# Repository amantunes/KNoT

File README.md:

# KNoT High Precision IoT Sensor Node

This sensor node was developed as a master's thesis project, with the objective of achieving high precision measurements of several sensors of any type, including those which can present some challenges such as water conductivity or pH sensors.

In order to achieve this a Cypress PSoC 5LP Microcontroller was used due to its 20-bit internal ADC, alongside an optional Analog Devices AD5941 High Precision, Impedance & Electrochemical Front End.

Wired communications are handled by various protocols, such as I2C, SPI and UART, while wireless communications are handled by a u-blox SARA N2 NB-IoT module.

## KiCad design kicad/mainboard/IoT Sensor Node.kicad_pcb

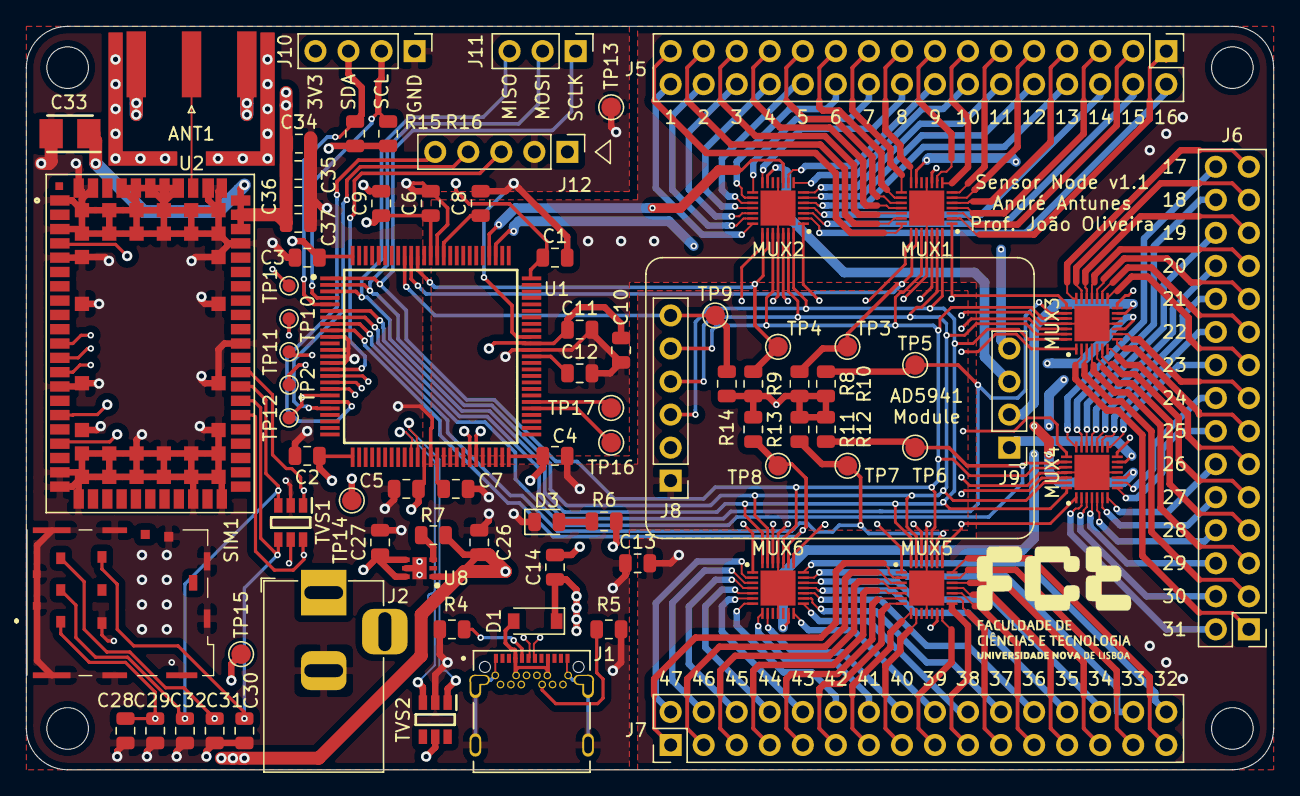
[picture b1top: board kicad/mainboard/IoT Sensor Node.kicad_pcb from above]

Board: 4 copper layers, 95.9 x 57.2 mm, 81 parts (0 on the bottom side), 147 nets.

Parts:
ANT1: Conn_Coaxial; SMA_Amphenol_132289_EdgeMount
C1, C2, C3, C4, C5, C6, C11, C28, C34: 0.1uF; C_0805_2012Metric
C7, C8, C9, C10, C12, C13, C14: 1uF; C_0805_2012Metric
C26, C27: 4.7uF; C_0805_2012Metric
C29, C30, C31, C32: 33pF; C_0805_2012Metric
C33: 100uF; CAPPM3528X210N
C35: 10nF; C_0805_2012Metric
C36: 68pF; C_0805_2012Metric
C37: 15pF; C_0805_2012Metric
D1: PMEG2010ER; D_SOD-123
D3: LED; LED_0805_2012Metric
J1: UJ31-CH-31N-SMT-TR; CUI_UJ31-CH-3-SMT-TR
J2: Jack-DC; BarrelJack_Horizontal
J5, J7: Conn_02x16_Odd_Even; PinHeader_2x16_P2.54mm_Vertical
J6: Conn_02x15_Odd_Even; PinHeader_2x15_P2.54mm_Vertical
J8: Conn_01x06; PinHeader_1x06_P2.54mm_Vertical
J9, J10: Conn_01x04; PinHeader_1x04_P2.54mm_Vertical
J11: Conn_01x03; PinHeader_1x03_P2.54mm_Vertical
J12: Conn_01x05; PinHeader_1x05_P2.54mm_Vertical
MUX1, MUX2, MUX3, MUX4, MUX5, MUX6: MAX14661ETI+; QFN40P400X400X80-29N
R4, R5: 5.1KR; R_0805_2012Metric
R6: 1KR; R_0805_2012Metric
R7, R8, R9, R10, R11, R12, R13, R14, R15, R16: 10KR; R_0805_2012Metric
SIM1: SF72S006VBAR2500
TP1, TP2, TP10, TP11, TP12: TestPoint; TestPoint_Pad_D1.0mm
TP3, TP4, TP5, TP6, TP7, TP8, TP9, TP13, TP14, TP15, TP16, TP17: TestPoint; TestPoint_Pad_D1.5mm
TVS1, TVS2: CM1293A-04SO; SOP95P275X110-6N
U1: CY8C5888AXI-LP096; QFP50P1600X1600X145-100N
U2: SARA-N210
U8: LP5912-3.3DRVR; SON65P200X200X80-7N

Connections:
3.3V: C3.1, C26.1, C33.1, C34.1, C35.1, C36.1, C37.1, J8.2, J10.4, MUX1.1, MUX1.22, MUX1.26, MUX2.1, MUX2.22, MUX2.26, MUX3.1, MUX3.22, MUX3.26, MUX4.1, MUX4.22, MUX4.26, MUX5.1, MUX5.22, MUX5.26, MUX6.1, MUX6.22, MUX6.26, R6.2, R7.2, R8.2, R9.2, R10.2, R11.2, R12.2, R13.2, R14.2, R15.2, R16.2, TP15.1, U1.100, U2.51, U2.52, U2.53, U8.1
AD5941_CS: J8.6, R14.1, TP9.1, U1.92
I2C_3V3_SCL: J10.2, R16.1, U1.4
I2C_3V3_SDA: J10.3, R15.1, U1.5
MUX1_1: J5.1, MUX1.2
MUX1_2: J5.3, MUX1.3
MUX1_3: J5.5, MUX1.4
MUX1_4: J5.7, MUX1.5
MUX1_5: J5.9, MUX1.6
MUX1_6: J5.11, MUX1.7
MUX1_7: J5.13, MUX1.8
MUX1_8: J5.15, MUX1.9
MUX1_9: J5.31, MUX1.21
MUX1_10: J5.29, MUX1.20
MUX1_11: J5.27, MUX1.19
MUX1_12: J5.25, MUX1.18
MUX1_13: J5.23, MUX1.17
MUX1_14: J5.21, MUX1.16
MUX1_15: J5.19, MUX1.15
MUX1_16: J5.17, MUX1.14
MUX1_A: MUX1.10, U1.78
MUX1_B: J9.4, MUX1.13
MUX1_CS: MUX1.23, R8.1, TP3.1, U1.91
MUX2_1: J5.2, MUX2.2
MUX2_2: J5.4, MUX2.3
MUX2_3: J5.6, MUX2.4
MUX2_4: J5.8, MUX2.5
MUX2_5: J5.10, MUX2.6
MUX2_6: J5.12, MUX2.7
MUX2_7: J5.14, MUX2.8
MUX2_8: J5.16, MUX2.9
MUX2_9: J5.32, MUX2.21
MUX2_10: J5.30, MUX2.20
MUX2_11: J5.28, MUX2.19
MUX2_12: J5.26, MUX2.18
MUX2_13: J5.24, MUX2.17
MUX2_14: J5.22, MUX2.16
MUX2_15: J5.20, MUX2.15
MUX2_16: J5.18, MUX2.14
MUX2_A: MUX2.10, U1.79
MUX2_B: J9.3, MUX2.13
MUX2_CS: MUX2.23, R9.1, TP4.1, U1.90
MUX3_1: J6.1, MUX3.2
MUX3_2: J6.3, MUX3.3
MUX3_3: J6.5, MUX3.4
MUX3_4: J6.7, MUX3.5
MUX3_5: J6.9, MUX3.6
MUX3_6: J6.11, MUX3.7
MUX3_7: J6.13, MUX3.8
MUX3_8: J6.15, MUX3.9
MUX3_9: J6.29, MUX3.21
MUX3_10: J6.27, MUX3.20
MUX3_11: J6.25, MUX3.19
MUX3_12: J6.23, MUX3.18
MUX3_13: J6.21, MUX3.17
MUX3_14: J6.19, MUX3.16
MUX3_15: J6.17, MUX3.15
MUX3_A: MUX3.10, U1.44
MUX3_B: J9.2, MUX3.13
MUX3_CS: MUX3.23, R10.1, TP5.1, U1.6
MUX4_1: J6.2, MUX4.2
MUX4_2: J6.4, MUX4.3
MUX4_3: J6.6, MUX4.4
MUX4_4: J6.8, MUX4.5
MUX4_5: J6.10, MUX4.6
MUX4_6: J6.12, MUX4.7
MUX4_7: J6.14, MUX4.8
MUX4_8: J6.16, MUX4.9
MUX4_9: J6.30, MUX4.21
MUX4_10: J6.28, MUX4.20
MUX4_11: J6.26, MUX4.19
MUX4_12: J6.24, MUX4.18
MUX4_13: J6.22, MUX4.17
MUX4_14: J6.20, MUX4.16
MUX4_15: J6.18, MUX4.15
MUX4_A: MUX4.10, U1.45
MUX4_B: J9.1, MUX4.13
MUX4_CS: MUX4.23, R11.1, TP6.1, U1.7
MUX5_1: J7.1, MUX5.2
MUX5_2: J7.3, MUX5.3
MUX5_3: J7.5, MUX5.4
MUX5_4: J7.7, MUX5.5
MUX5_5: J7.9, MUX5.6
MUX5_6: J7.11, MUX5.7
MUX5_7: J7.13, MUX5.8
MUX5_8: J7.15, MUX5.9
MUX5_9: J7.31, MUX5.21
MUX5_10: J7.29, MUX5.20
MUX5_11: J7.27, MUX5.19
MUX5_12: J7.25, MUX5.18
MUX5_13: J7.23, MUX5.17
MUX5_14: J7.21, MUX5.16
MUX5_15: J7.19, MUX5.15
MUX5_16: J7.17, MUX5.14
MUX5_B: MUX4.14, MUX5.13
MUX5_CS: MUX5.23, R12.1, TP7.1, U1.8
MUX6_1: J7.2, MUX6.2
MUX6_2: J7.4, MUX6.3
MUX6_3: J7.6, MUX6.4
MUX6_4: J7.8, MUX6.5
MUX6_5: J7.10, MUX6.6
MUX6_6: J7.12, MUX6.7
MUX6_7: J7.14, MUX6.8
MUX6_8: J7.16, MUX6.9
MUX6_9: J7.32, MUX6.21
MUX6_10: J7.30, MUX6.20
MUX6_11: J7.28, MUX6.19
MUX6_12: J7.26, MUX6.18
MUX6_13: J7.24, MUX6.17
MUX6_14: J7.22, MUX6.16
MUX6_15: J7.20, MUX6.15
MUX6_16: J7.18, MUX6.14
MUX6_B: MUX3.14, MUX6.13
MUX6_CS: MUX6.23, R13.1, TP8.1, U1.9
unnamed: D1.2, J1.A4, J1.A9, J1.B4, J1.B9
unnamed: D3.2, R6.1
unnamed: J1.A5, R4.1
unnamed: J1.B5, R5.1
unnamed: R7.1, U8.3
unnamed: TP1.1, U2.4
unnamed: TP2.1, U2.16
unnamed: TP16.1, U1.55
unnamed: TP17.1, U1.56
RST: J12.3, U1.15
SARA_ANT: ANT1.1, U2.56
SARA_CTS: U1.16, U2.11
SARA_RESET: TP12.1, U1.19, U2.18
SARA_RXD: TP11.1, U1.18, U2.13
SARA_SIM_CLK: C31.1, SIM1.C3, TVS1.6, U2.38
SARA_SIM_IO: C30.1, SIM1.C7, TVS1.4, U2.39
SARA_SIM_RST: C32.1, SIM1.C2, TVS1.3, U2.40
SARA_TXD: TP10.1, U1.17, U2.12
SARA_VSIM: C28.1, C29.1, SIM1.C1, TVS1.1, U2.41
SPI_MISO: J8.3, J11.3, MUX1.28, MUX2.28, MUX3.28, MUX4.28, MUX5.28, MUX6.28, U1.3
SPI_MOSI: J8.4, J11.2, MUX1.27, MUX2.27, MUX3.27, MUX4.27, MUX5.27, MUX6.27, U1.2
SPI_SCLK: J8.5, J11.1, MUX1.24, MUX2.24, MUX3.24, MUX4.24, MUX5.24, MUX6.24, U1.1
SWDCLK: J12.4, U1.21
SWDIO: J12.5, U1.20
USB+: J1.A6, J1.B6, TVS2.3, U1.35
USB-: J1.A7, J1.B7, TVS2.1, U1.36
VBAT: ANT1.2, C1.2, C2.2, C3.2, C4.2, C5.2, C6.2, C7.2, C8.2, C9.2, C13.1, C26.2, C27.2, C28.2, C29.2, C30.2, C31.2, C32.2, C33.2, C34.2, C35.2, C36.2, C37.2, D3.1, J1.A1, J1.A12, J1.B1, J1.B12, J1.SH1, J1.SH2, J1.SH3, J1.SH4, J1.SH5, J1.SH6, J2.2, J8.1, J10.1, J12.2, MUX1.11, MUX1.25, MUX1.29, MUX2.11, MUX2.25, MUX2.29, MUX3.11, MUX3.25, MUX3.29, MUX4.11, MUX4.25, MUX4.29, MUX5.11, MUX5.25, MUX5.29, MUX6.11, MUX6.25, MUX6.29, R4.2, R5.2, SIM1.C5, SIM1.GND1, SIM1.GND2, SIM1.GND3, SIM1.GND4, SIM1.GND5, SIM1.GND6, SIM1.GND7, SIM1.GND8, SIM1.GND9, SIM1.GND10, TP13.1, TVS1.2, TVS2.2, U1.10, U1.12, U1.13, U1.14, U1.38, U1.66, U1.87, U2.1, U2.3, U2.5, U2.14, U2.20, U2.21, U2.22, U2.30, U2.32, U2.43, U2.50, U2.54, U2.55, U2.57, U2.58, U2.59, U2.60, U2.61, U2.63, U2.64, U2.65, U2.66, U2.67, U2.68, U2.69, U2.70, U2.71, U2.72, U2.73, U2.74, U2.75, U2.76, U2.77, U2.78, U2.79, U2.80, U2.81, U2.82, U2.83, U2.84, U2.85, U2.86, U2.87, U2.88, U2.89, U2.90, U2.91, U2.92, U2.93, U2.94, U2.95, U2.96, U8.5, U8.7
VCC1: C7.1, U1.39
VCC2: C8.1, U1.86
VCCA: C12.1, U1.63
VDD1: C1.1, C2.1, C4.1, C5.1, C6.1, C9.1, C14.1, C27.1, D1.1, J2.1, J12.1, TP14.1, TVS1.5, TVS2.5, U1.26, U1.37, U1.50, U1.75, U1.88, U8.4, U8.6
VDDA: C10.1, C11.1, C14.2, U1.65
VSSA: C10.2, C11.2, C12.2, C13.2, U1.64

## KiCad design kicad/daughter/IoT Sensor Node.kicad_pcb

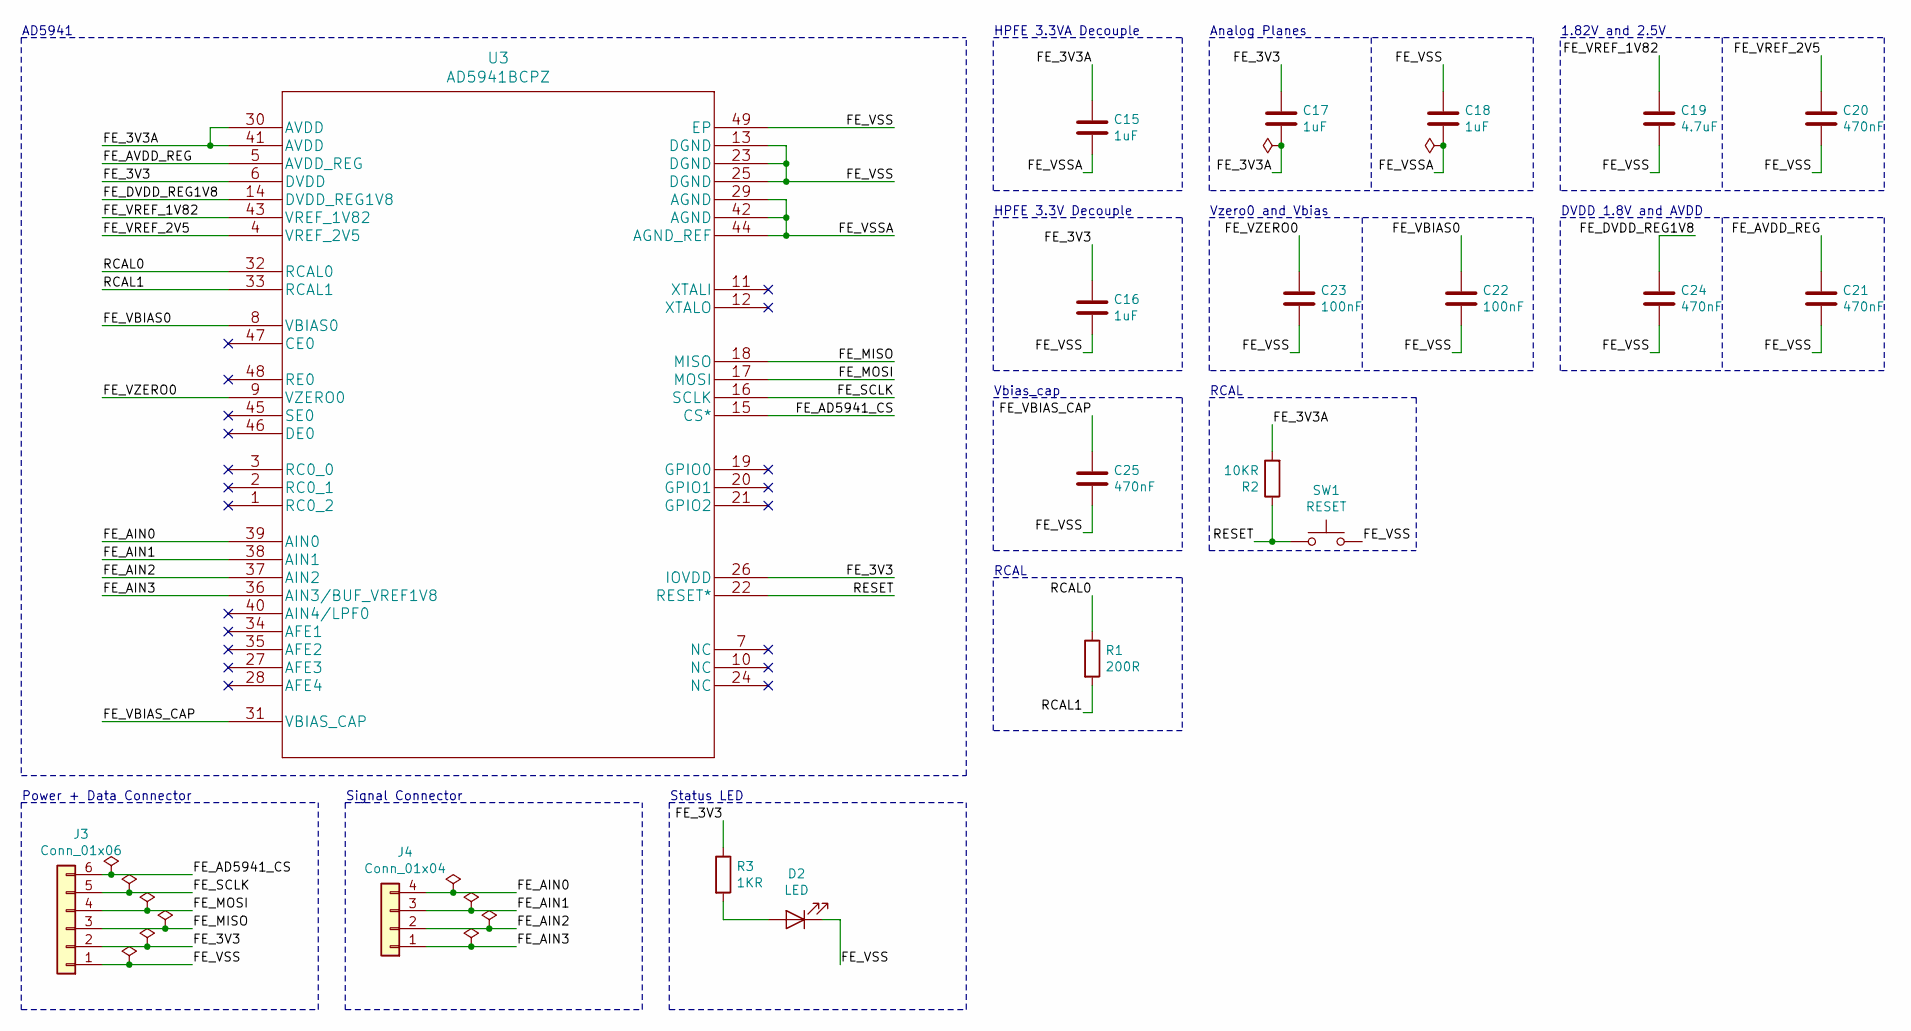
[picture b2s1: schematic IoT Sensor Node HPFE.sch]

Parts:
C15, C16, C17, C18: 1uF; C_0805_2012Metric
C19: 4.7uF; C_0805_2012Metric
C20, C21, C24, C25: 470nF; C_0805_2012Metric
C22, C23: 100nF; C_0805_2012Metric
D2: LED; LED_0805_2012Metric
J3: Conn_01x06; PinSocket_1x06_P2.54mm_Vertical
J4: Conn_01x04; PinSocket_1x04_P2.54mm_Vertical
R1: 200R; R_0805_2012Metric
R2: 10KR; R_0805_2012Metric
R3: 1KR; R_0805_2012Metric
SW1: RESET; PTS815SJM250SMTR
U3: AD5941BCPZ; QFN50P700X700X80-49N-D

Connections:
/IoT Sensor Node HPFE/FE_3V3: C16.1, C17.1, J3.2, R3.1, U3.6 (DVDD), U3.26 (IOVDD)
/IoT Sensor Node HPFE/FE_3V3A: C15.1, C17.2, R2.2, U3.30 (AVDD), U3.41 (AVDD)
/IoT Sensor Node HPFE/FE_AD5941_CS: J3.6, U3.15 (CS*)
/IoT Sensor Node HPFE/FE_AIN0: J4.4, U3.39 (AIN0)
/IoT Sensor Node HPFE/FE_AIN1: J4.3, U3.38 (AIN1)
/IoT Sensor Node HPFE/FE_AIN2: J4.2, U3.37 (AIN2)
/IoT Sensor Node HPFE/FE_AIN3: J4.1, U3.36 (AIN3/BUF_VREF1V8)
/IoT Sensor Node HPFE/FE_AVDD_REG: C21.1, U3.5 (AVDD_REG)
/IoT Sensor Node HPFE/FE_DVDD_REG1V8: C24.1, U3.14 (DVDD_REG1V8)
/IoT Sensor Node HPFE/FE_MISO: J3.3, U3.18 (MISO)
/IoT Sensor Node HPFE/FE_MOSI: J3.4, U3.17 (MOSI)
/IoT Sensor Node HPFE/FE_SCLK: J3.5, U3.16 (SCLK)
/IoT Sensor Node HPFE/FE_VBIAS0: C22.1, U3.8 (VBIAS0)
/IoT Sensor Node HPFE/FE_VBIAS_CAP: C25.1, U3.31 (VBIAS_CAP)
/IoT Sensor Node HPFE/FE_VREF_1V82: C19.1, U3.43 (VREF_1V82)
/IoT Sensor Node HPFE/FE_VREF_2V5: C20.1, U3.4 (VREF_2V5)
/IoT Sensor Node HPFE/FE_VSS: C16.2, C18.1, C19.2, C20.2, C21.2, C22.2, C23.2, C24.2, C25.2, D2.1 (K), J3.1, SW1.2, U3.13 (DGND), U3.23 (DGND), U3.25 (DGND), U3.49 (EP)
/IoT Sensor Node HPFE/FE_VSSA: C15.2, C18.2, U3.29 (AGND), U3.42 (AGND), U3.44 (AGND_REF)
/IoT Sensor Node HPFE/FE_VZERO0: C23.1, U3.9 (VZERO0)
/IoT Sensor Node HPFE/RCAL0: R1.1, U3.32 (RCAL0)
/IoT Sensor Node HPFE/RCAL1: R1.2, U3.33 (RCAL1)
/IoT Sensor Node HPFE/RESET: R2.1, SW1.1, U3.22 (RESET*)
unnamed: D2.2 (A), R3.2

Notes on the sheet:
AD5941
HPFE 3.3V Decouple
HPFE 3.3VA Decouple
1.82V and 2.5V
Analog Planes
DVDD 1.8V and AVDD
Vzero0 and Vbias
Vbias_cap
RCAL
Power + Data Connector
Signal Connector
Status LED

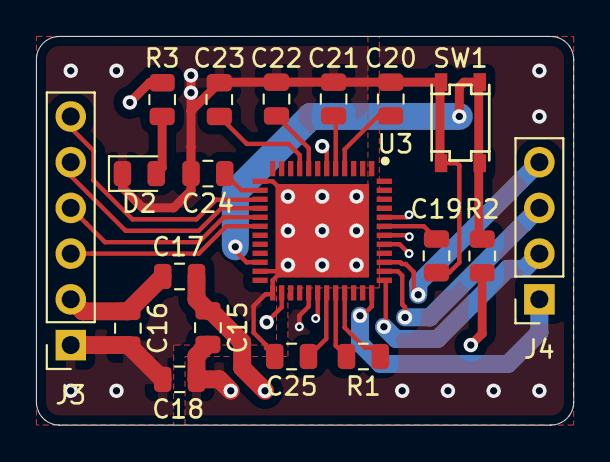
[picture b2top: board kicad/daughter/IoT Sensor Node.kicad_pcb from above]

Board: 4 copper layers, 29.8 x 21.6 mm, 19 parts (0 on the bottom side), 23 nets.

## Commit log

2021-01-19 Gerbers Added
2021-01-19 Added KiCad Files
2021-01-19 Libraries Added
2021-01-27 Added the results section
2021-01-31 Added PSoC Creator Project
